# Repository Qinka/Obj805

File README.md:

# Obj805

## "Funny"

So the "Funny" is an Easter egg.
There provides some function to control the dc value of fan in specific function.

The most import function provided is `DTFT`, and with given coefficients and scalers,
we can output most common signal of dc.

The first thing to do is to enter the "funny" mode.
You need to launch the console of browser and then run `runFunny`.
All the command run in funny's input text box can be executed in console.

Secondly, you need to load the `library/extension.js` script.
You should run the `loadScript('library/extension.js')` in input text box or console.

Thirdly, run the `DTFT()`. `DTFT` is defined with parameters:
```javascript
function DTFT(sca,coe,value,coe_,bias,delay) {...}
```
`sca` and `coe` are the scalar and frequency of DTFT.
`value` is the begining value of loop, and it is usually `0`.
`coe_` and `bias` is the transformation parameter of hold function.
`delay` is the update delay(microsecond).

### Example (old version with DTFT)

```javascript
sca = [1,0.5,0.25,0.125,0.0625,0.0313,0.0156,0.0078];
coe = [0,1,2,3,4,5,6,7];
DTFT(sca,coe,0,0.7531,-0.5003,100);
```

### Example (new version with mkSim)

To make a square wave:
```javascript
sca=[1,1/3,1/5,1/7];
coe=[1,3,5,7];
sq=mkSim(sca,coe,Math.sin);
timeoutNV(sq,50,50,0,0.1,300);
```

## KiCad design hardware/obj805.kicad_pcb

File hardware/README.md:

Snapshot for Obj805 hardware (ReadMe)
===

## Hardware list

1. Fan (no on pcb)

2. L293d

3. leds
    - Service connected
    - PWM
    - button passed

4. Segment Displays

5. Buttons

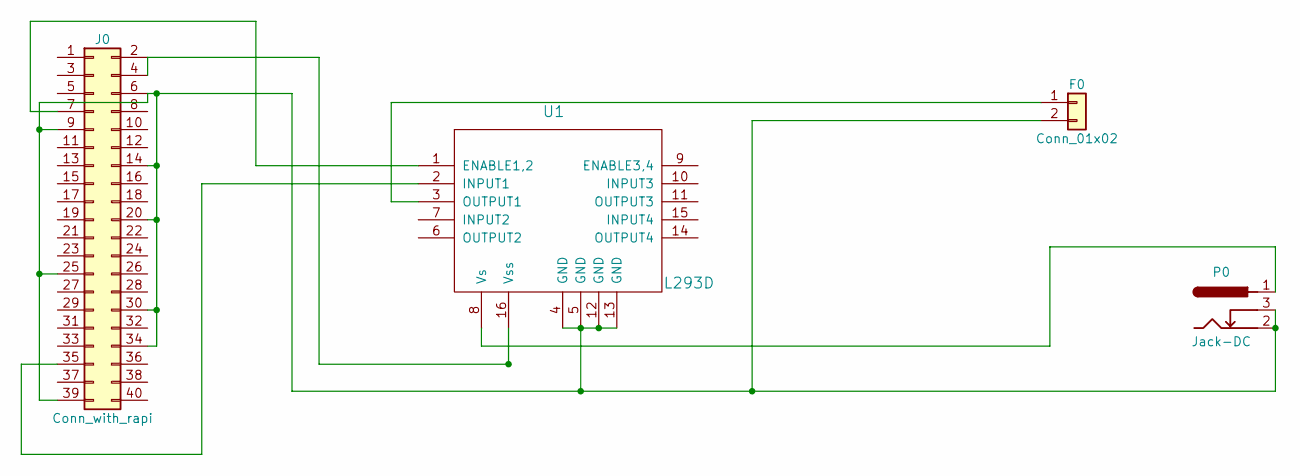
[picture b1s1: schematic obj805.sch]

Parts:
F0: Conn_01x02; Pin_Header_Straight_1x02_Pitch2.54mm
J0: Conn_with_rapi; Pin_Header_Straight_2x20_Pitch2.54mm
P0: Jack-DC; JACK_ALIM
U1: L293D

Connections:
unnamed: F0.1, U1.3 (OUTPUT1)
unnamed: F0.2, J0.6, J0.9, J0.14, J0.20, J0.25, J0.30, J0.34, J0.39, P0.2, P0.3, U1.4 (GND), U1.5 (GND), U1.12 (GND), U1.13 (GND)
unnamed: J0.2, J0.4, U1.16 (Vss)
unnamed: J0.7, U1.1 (ENABLE1,2)
unnamed: J0.35, U1.2 (INPUT1)
unnamed: P0.1, U1.8 (Vs)

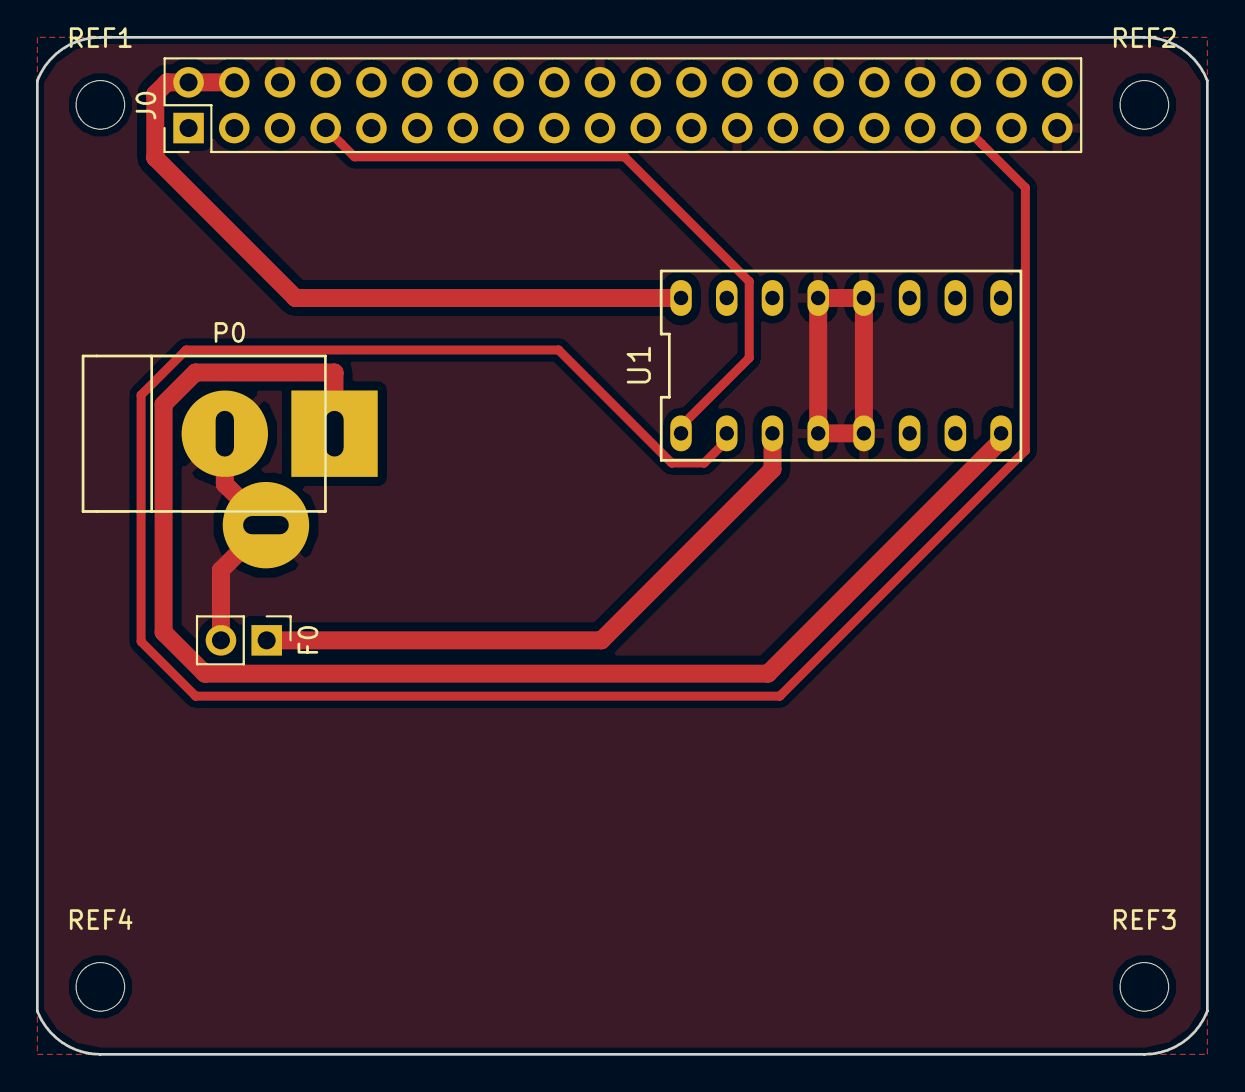
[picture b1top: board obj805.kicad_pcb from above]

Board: 2 copper layers, 65.0 x 56.5 mm, 8 parts (0 on the bottom side), 6 nets.

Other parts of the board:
REF1, REF2, REF3, REF4: MountingHole_2.7mm_M2.5

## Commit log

2016-02-02 init
2017-01-27 init;
2017-07-01 for v-bis-m
2017-07-01 add the gpio
2017-07-01 rewrite gpio
2017-07-01 fix place
2017-07-03 fix the error using for static
2017-07-03 restruct
2017-07-03 add the a header file
2017-07-03 rewrite
2017-07-03 rename
2017-07-11 add pcb design
2017-07-11 change
2017-07-11 add another pcb for L293d
2017-07-12 add the hole for screw
2017-11-10 remove
2017-11-10 add l293d, and connect the circut(undone)
2017-12-17 update;
2017-12-31 update, try for ci
2018-01-01 update; fix the errors in script of CI
2018-01-02 update; fix the error in succ.sh
2018-01-02 back-end test well and front-end worked; whole system is worked.
2018-01-02 update;; checkpoint
2018-01-03 update; add css and js
2018-01-04 add the auth(basic) of site
2018-01-04 replace url with text for some url can not pass pattern test
2018-01-04 change for http and https for more add author for host.py
2018-01-04 add host.run to easilier to run python codes
2018-01-04 add docker stack
2018-01-06 update add some extensions
2018-01-08 Update README.md
    fix some spell error
2018-01-20 update the extension.js to get the wave function.
